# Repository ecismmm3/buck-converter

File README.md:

# buck-converter
5V 1A DC-DC Buck Converter

## Electrical Components

- LM2596S-5.0 IC
- Screwdriver Terminal Blocks (x2)
- Capacitors (C1 = 470uF 50V, C2 = 330uF 25V)
- Inductor (33 uH)
- 1N5820 Schottky Diode (x1)

## Testing (simulation)

- 5 ohm test load (simulate 5V 1A)

Schematic + SPICE Directives (custom parts found in `LTSpice/`):

Voltage Plot:

- Green: Input
- Blue: Output
- Red: duty cycle

Current Plot:

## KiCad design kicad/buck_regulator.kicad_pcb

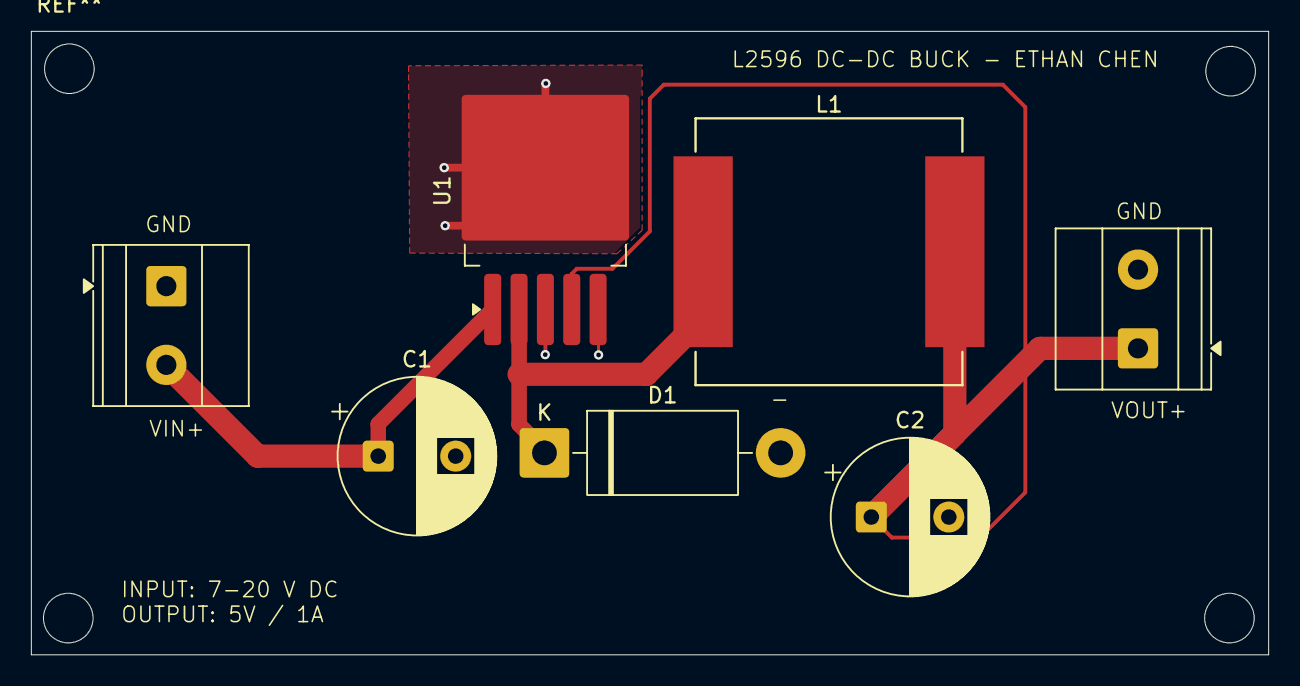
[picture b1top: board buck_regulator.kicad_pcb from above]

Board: 2 copper layers, 79.8 x 40.2 mm, 7 parts (0 on the bottom side), 4 nets.

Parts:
C1: 470uF 50V; CP_Radial_D10.0mm_P5.00mm
C2: 330uF 35V; CP_Radial_D10.0mm_P5.00mm
D1: 1N5822; D_DO-201AD_P15.24mm_Horizontal
J1, J2: Screw_Terminal_01x02; TerminalBlock_Phoenix_MKDS-1,5-2-5.08_1x02_P5.08mm_Horizont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
L1: 33uH; L_Vishay_IHLP-6767
U1: LM2596S-5; TO-263-5_TabPin3

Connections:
GND: C1.2, C2.2, D1.2 (A), J1.2, J2.1, U1.3 (GND), U1.5 (~ON/OFF)
unnamed: D1.1 (K), L1.1, U1.2 (OUT)
unnamed: C2.1, J1.1, L1.2, U1.4 (FB)
unnamed: C1.1, J2.2, U1.1 (VIN)
